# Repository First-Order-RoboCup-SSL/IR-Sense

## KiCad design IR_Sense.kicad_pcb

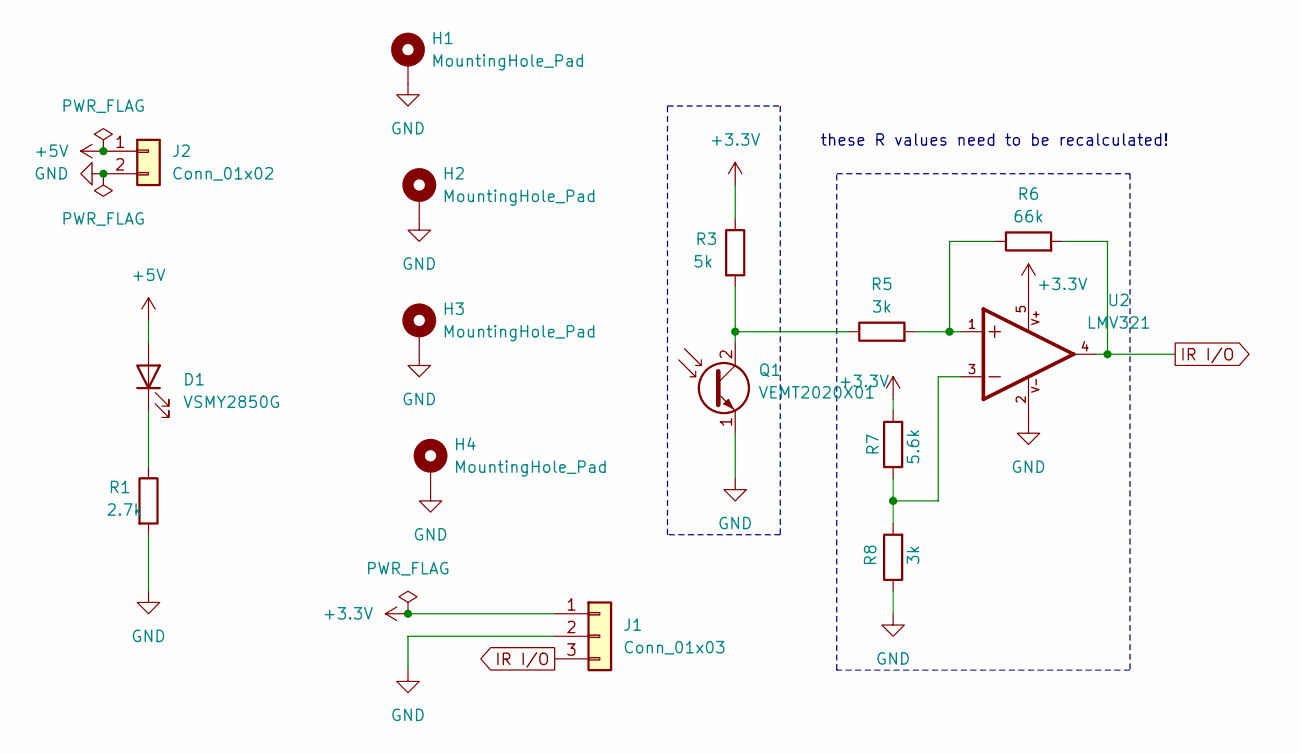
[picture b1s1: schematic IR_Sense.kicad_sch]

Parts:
D1: VSMY2850G; VSMY2850G_VEMT2020X01
H1, H2, H3, H4: MountingHole_Pad; MountingHole_2.2mm_M2_DIN965_Pad
J1: Conn_01x03; J1-SMD_PADS_ONLY
J2: Conn_01x02; Tx_Power_Pads
Q1: VEMT2020X01; VSMY2850G_VEMT2020X01
R1: 2.7k; R_0603_1608Metric_Pad0.98x0.95mm_HandSolder
R3: 5k; R_0603_1608Metric_Pad0.98x0.95mm_HandSolder
R5, R8: 3k; R_0603_1608Metric_Pad0.98x0.95mm_HandSolder
R6: 66k; R_0603_1608Metric_Pad0.98x0.95mm_HandSolder
R7: 5.6k; R_0603_1608Metric_Pad0.98x0.95mm_HandSolder
U2: LMV321; SOT-23-5

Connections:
+3.3V: J1.1, R3.1, R7.2, U2.5
+5V: D1.2 (A), J2.1
GND: H1.1, H2.1, H3.1, H4.1, J1.2, J2.2, Q1.1 (E), R1.2, R8.1, U2.2
IR I/O: J1.3, R6.2, U2.4
unnamed: D1.1 (K), R1.1
unnamed: Q1.2 (C), R3.2, R5.1
unnamed: R5.2, R6.1, U2.1
unnamed: R7.1, R8.2, U2.3

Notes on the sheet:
these R values need to be recalculated!

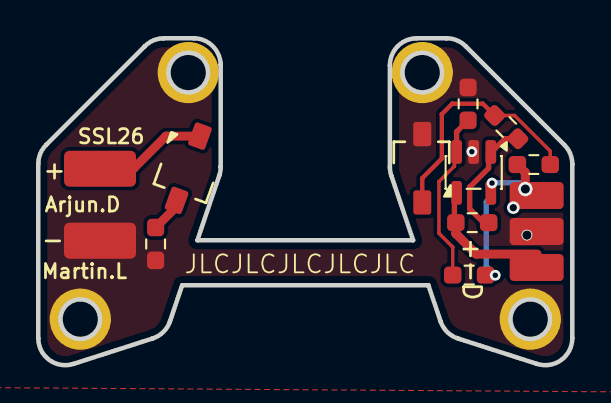
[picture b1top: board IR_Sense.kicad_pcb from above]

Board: 2 copper layers, 29.7 x 18.2 mm, 15 parts (0 on the bottom side), 8 nets.

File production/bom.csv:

Designator,Footprint,Quantity,Value,LCSC Part #
D1,VSMY2850G_VEMT2020X01,1,VSMY2850G,
J1,J1-SMD_PADS_ONLY,1,Conn_01x03,
J2,Tx_Power_Pads,1,Conn_01x02,
Q1,VSMY2850G_VEMT2020X01,1,VEMT2020X01,
R1,0603,1,2.7k,
R3,0603,1,5k,
"R5, R8",0603,2,3k,
R6,0603,1,66k,
R7,0603,1,5.6k,
U2,SOT-23-5,1,LMV321,

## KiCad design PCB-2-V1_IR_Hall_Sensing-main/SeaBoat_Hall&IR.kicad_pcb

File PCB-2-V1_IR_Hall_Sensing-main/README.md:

# 2025Seaboat_IR_and_Hall_Sensors
### Schematics 

main circuit for analog hall detector

main circuit for IR detector

### Layout

### PCB Preview

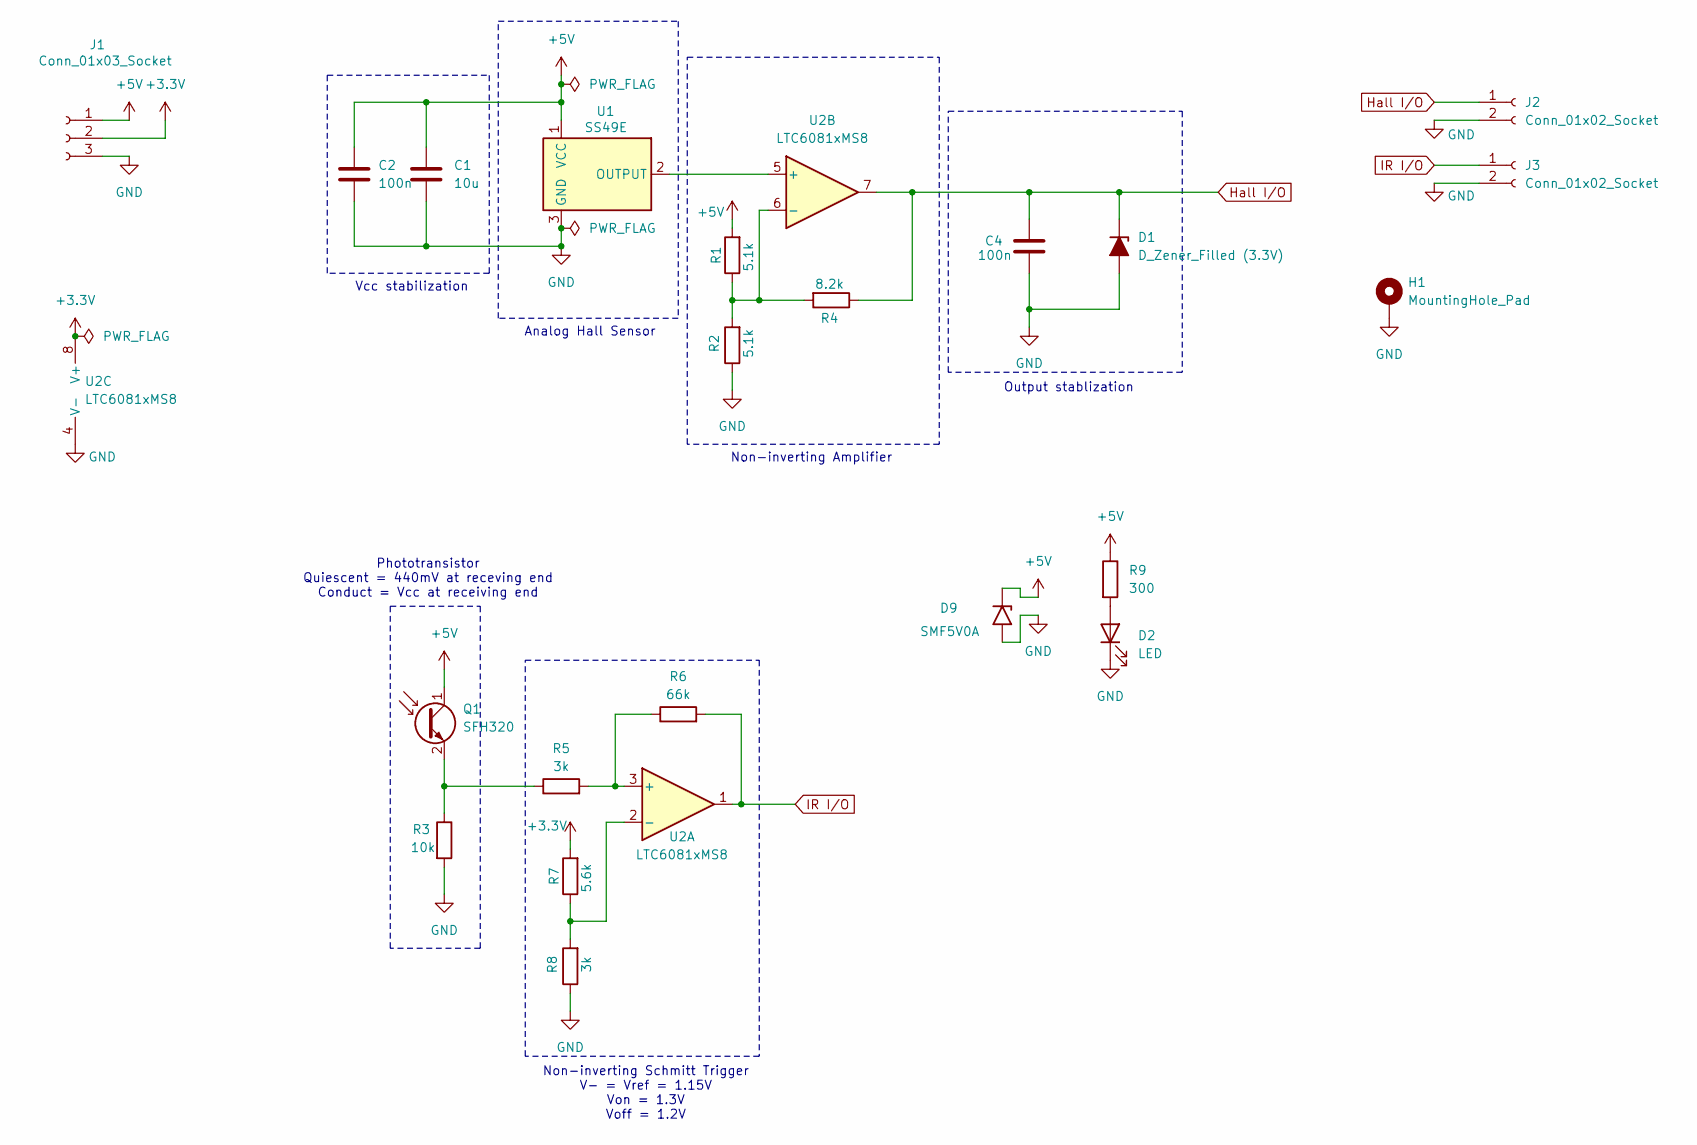
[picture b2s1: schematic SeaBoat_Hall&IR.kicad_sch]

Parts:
C1: 10u; C_0603_1608Metric_Pad1.08x0.95mm_HandSolder
C2, C4: 100n; C_0603_1608Metric_Pad1.08x0.95mm_HandSolder
D1: D_Zener_Filled (3.3V); D_SOD-123
D2: LED; LED_0603_1608Metric_Pad1.05x0.95mm_HandSolder
D9: SMF5V0A; D_SMF
H1: MountingHole_Pad; MountingHole_3.2mm_M3_DIN965_Pad
J1: Conn_01x03_Socket; JST_GH_BM03B-GHS-TBT_1x03-1MP_P1.25mm_Vertical
J2, J3: Conn_01x02_Socket; U.FL_Molex_MCRF_73412-0110_Vertical
Q1: SFH320; LED_PLCC-2_3.4x3.0mm_KA
R1, R2: 5.1k; R_0603_1608Metric_Pad0.98x0.95mm_HandSolder
R3: 10k; R_0603_1608Metric_Pad0.98x0.95mm_HandSolder
R4: 8.2k; R_0603_1608Metric_Pad0.98x0.95mm_HandSolder
R5, R8: 3k; R_0603_1608Metric_Pad0.98x0.95mm_HandSolder
R6: 66k; R_0603_1608Metric_Pad0.98x0.95mm_HandSolder
R7: 5.6k; R_0603_1608Metric_Pad0.98x0.95mm_HandSolder
R9: 300; R_0603_1608Metric_Pad0.98x0.95mm_HandSolder
U1: SS49E; SOT-23
U2: LTC6081xMS8; MSOP-8-1EP_3x3mm_P0.65mm_EP1.68x1.88mm

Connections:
+3.3V: J1.2, R7.2, U2.8 (V+)
+5V: C1.1, C2.1, D9.1 (A1), J1.1, Q1.1 (C), R1.2, R9.1, U1.1 (VCC)
GND: C1.2, C2.2, C4.2, D1.2 (A), D2.1 (K), D9.2 (A2), H1.1, J1.3, J2.2, J3.2, R2.1, R3.2, R8.1, U1.3 (GND), U2.4 (V-)
Hall I/O: C4.1, D1.1 (K), J2.1, R4.1, U2.7
IR I/O: J3.1, R6.2, U2.1
unnamed: D2.2 (A), R9.2
unnamed: Q1.2 (E), R3.1, R5.1
unnamed: U1.2 (OUTPUT), U2.5 (+)
unnamed: R5.2, R6.1, U2.3 (+)
unnamed: R7.1, R8.2, U2.2 (-)
unnamed: R1.1, R2.2, R4.2, U2.6 (-)

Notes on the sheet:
Phototransistor Quiescent = 440mV at receving end Conduct = Vcc at receiving end
Output stablization
Vcc stabilization
Analog Hall Sensor
Non-inverting Amplifier
Non-inverting Schmitt Trigger V- = Vref = 1.15V Von = 1.3V Voff = 1.2V

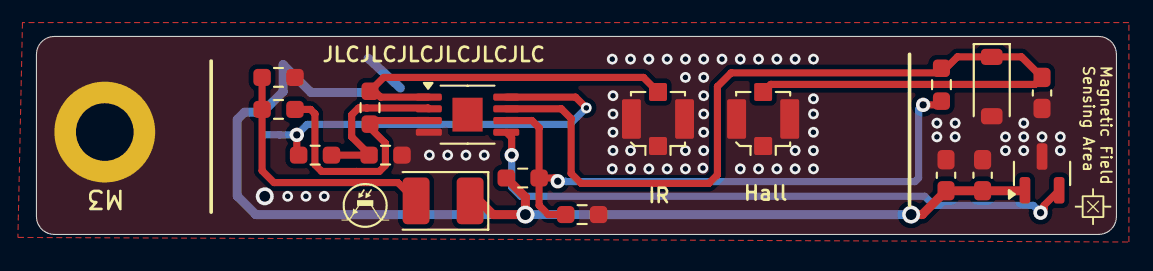
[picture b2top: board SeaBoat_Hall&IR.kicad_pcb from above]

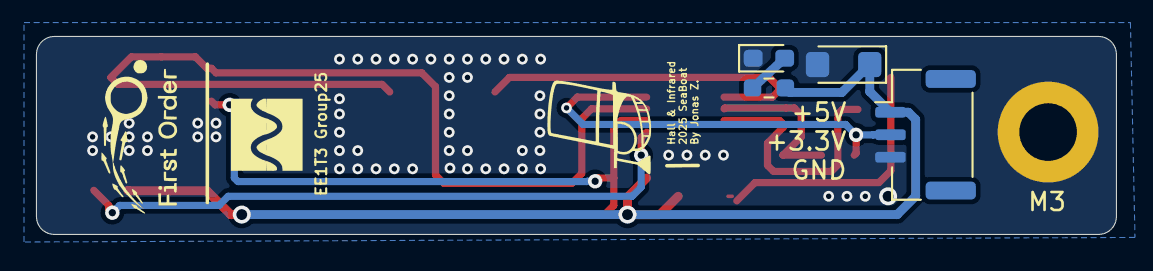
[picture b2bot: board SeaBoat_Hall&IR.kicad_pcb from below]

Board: 2 copper layers, 60.0 x 11.0 mm, 22 parts (4 on the bottom side), 11 nets.

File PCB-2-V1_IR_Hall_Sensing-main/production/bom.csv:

Designator,Footprint,Quantity,Value,LCSC Part #
C1,0603,1,10u,
"C2, C4",0603,2,100n,
D1,D_SOD-123,1,D_Zener_Filled (3.3V),
D2,0603,1,LED,
D9,D_SMF,1,SMF5V0A,
J1,JST_GH_BM03B-GHS-TBT_1x03-1MP_P1.25mm_Vertical,1,Conn_01x03_Socket,
"J2, J3",U.FL_Molex_MCRF_73412-0110_Vertical,2,Conn_01x02_Socket,
Q1,LED_PLCC-2_3.4x3.0mm_KA,1,SFH320,
"R1, R2",0603,2,5.1k,
R3,0603,1,10k,
R4,0603,1,8.2k,
"R5, R8",0603,2,3k,
R6,0603,1,66k,
R7,0603,1,5.6k,
R9,0603,1,R,
U1,SOT-23,1,SS49E,
U2,MSOP-8-1EP_3x3mm_P0.65mm_EP1.68x1.88mm,1,LTC6081xMS8,

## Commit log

2025-12-21 unpack file structure
2025-12-21 change IR diode and photo transistor
2025-12-27 reduced board size update
